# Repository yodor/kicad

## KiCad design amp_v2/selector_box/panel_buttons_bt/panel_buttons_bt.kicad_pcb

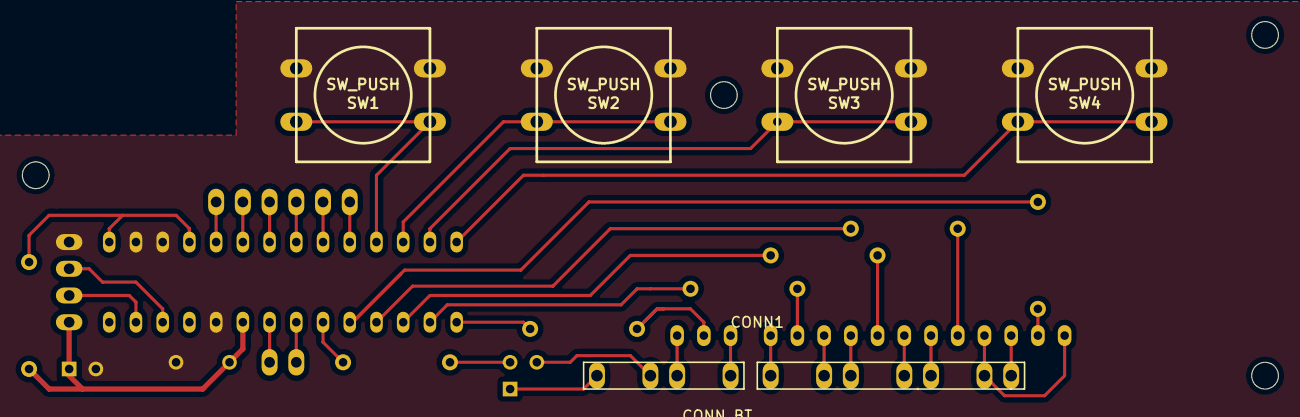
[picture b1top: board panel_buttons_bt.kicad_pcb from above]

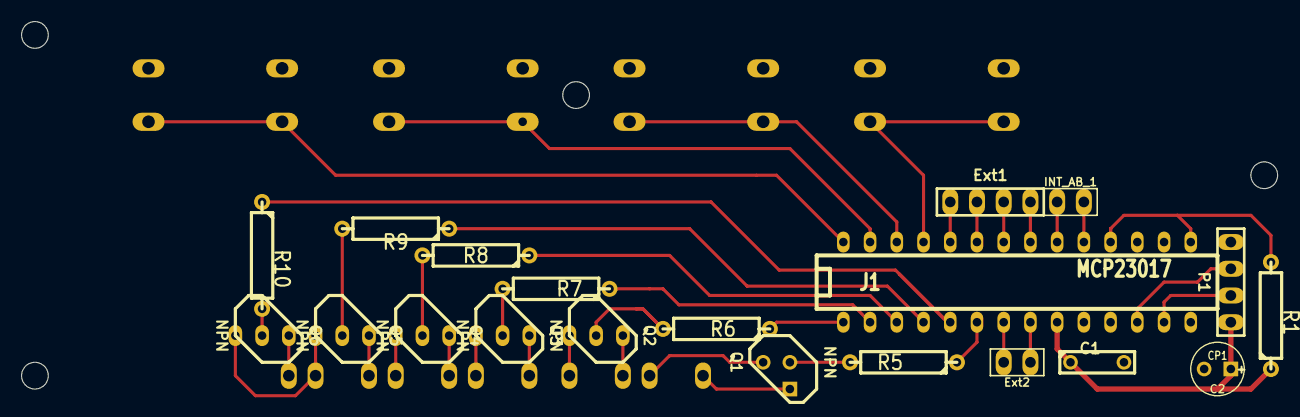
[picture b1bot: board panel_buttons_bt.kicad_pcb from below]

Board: 2 copper layers, 119.4 x 34.9 mm, 25 parts (20 on the bottom side), 40 nets.

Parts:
C1: 100nF; C2
C2: CP1; C1V5
CONN1: CONN_BT
Ext1: CONN_4; PIN_ARRAY_4x1
Ext2: CONN_2; PIN_ARRAY_2X1
INT_AB_1: CONN_2; PIN_ARRAY_2X1
J1: MCP23017; DIP-28__300
P1: CONN_4; PIN_ARRAY_4x1
Q1, Q2, Q3, Q4, Q5, Q6: NPN; TO92-123
R1, R5, R6, R7, R8, R9, R10: 10K; R4
SW1, SW2, SW3, SW4: SW_PUSH; SW_PUSH-12mm

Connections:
/5V: C1.1, C2.1, J1.9, P1.1, R1.1
/BTN1: J1.25, SW1.1
/BTN2: J1.26, SW2.1
/BTN3: J1.27, SW3.1
/BTN4: J1.28, SW4.1
/BT_BACK: J1.2, R7.1
/BT_FWD: J1.1, R6.1
/BT_PLPP: J1.5, R10.1
/BT_PWR: J1.6, R5.1
/BT_VOLDN: J1.4, R9.1
/BT_VOLUP: J1.3, R8.1
/SCL: J1.12, P1.3
/SDA: J1.13, P1.2
DGND: C1.2, C2.2, J1.10, J1.16, J1.17, P1.4, SW1.2, SW2.2, SW3.2, SW4.2
unnamed: Q3.2, R7.2
unnamed: CONN1.back, Q3.1
unnamed: CONN1.v_up, Q4.1
unnamed: CONN1.v_dn, Q5.1
unnamed: CONN1.play, Q6.1
unnamed: CONN1.1V81, Q2.3
unnamed: Q2.2, R6.2
unnamed: CONN1.fwd, Q2.1
unnamed: CONN1.1V82, Q3.3
unnamed: CONN1.pwr2, Q1.1
unnamed: Q4.2, R8.2
unnamed: Q5.2, R9.2
unnamed: Q6.2, R10.2
unnamed: CONN1.1V84, Q5.3, Q6.3
unnamed: CONN1.1V83, Q4.3
unnamed: Ext1.3, J1.22
unnamed: Ext1.1, J1.24
unnamed: Ext1.2, J1.23
unnamed: Ext1.4, J1.21
unnamed: INT_AB_1.1, J1.20
unnamed: INT_AB_1.2, J1.19
unnamed: Ext2.2, J1.7
unnamed: Ext2.1, J1.8
unnamed: J1.15, J1.18, R1.2
unnamed: Q1.2, R5.2
unnamed: CONN1.pwr1, Q1.3

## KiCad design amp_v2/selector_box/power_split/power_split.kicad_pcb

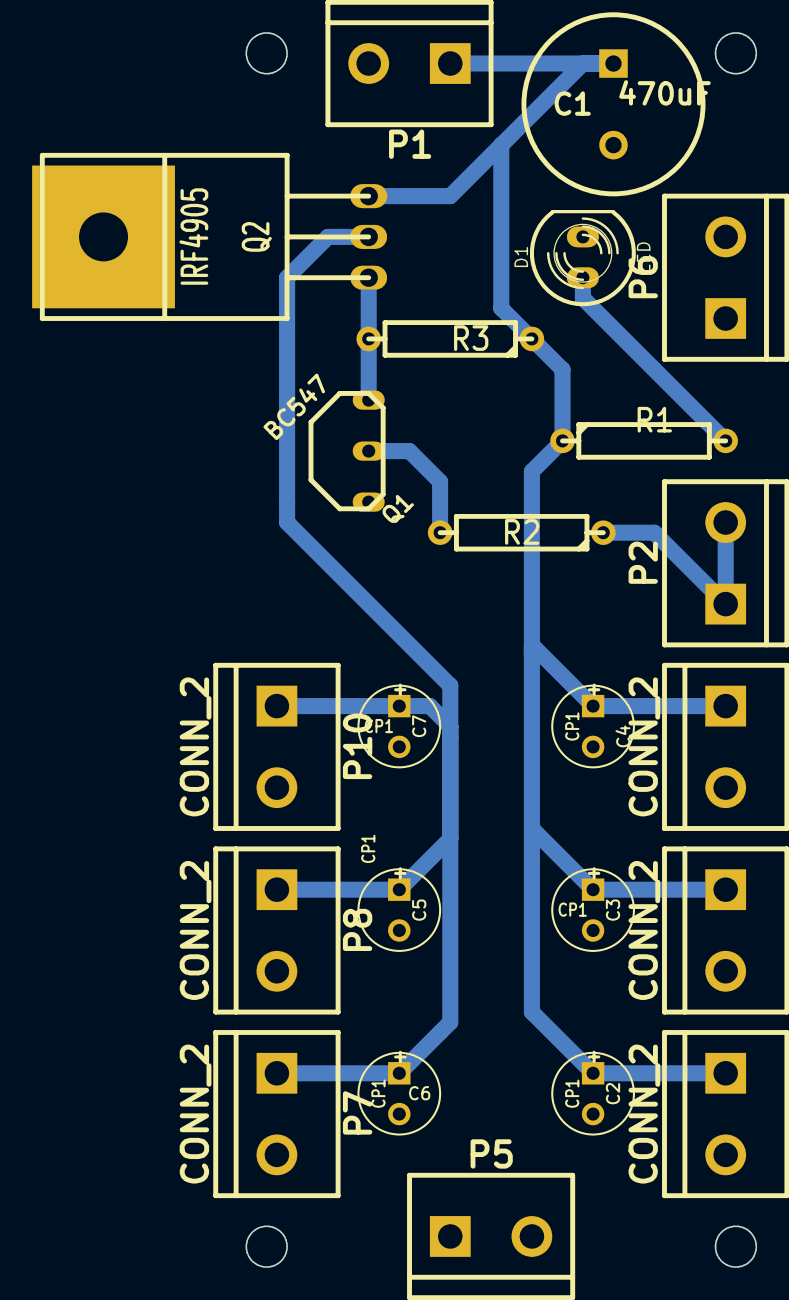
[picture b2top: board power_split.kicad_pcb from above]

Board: 2 copper layers, 31.8 x 76.8 mm, 23 parts (0 on the bottom side), 7 nets.

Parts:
C1: 470uF; C2V10
C2, C3, C4, C5, C6, C7: CP1; C1V5
D1: LED; LED-5MM
P1, P2, P3, P4, P5, P6, P7, P8, P9, P10: CONN_2; bornier2
Q1: BC547; TO92
Q2: IRF4905; TO220GDS
R1: 680R / 0.5W; R4
R2, R3: 10K; R4

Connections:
/12V: C1.1, C2.1, C3.1, C4.1, P1.1, P3.1, P4.1, P9.1, Q2.S, R1.1, R3.1
/12V_EN: P2.1, P2.2, R2.1
/12V_SW: C5.1, C6.1, C7.1, P7.1, P8.1, P10.1, Q2.D
GND: C1.2, C2.2, C3.2, C4.2, C5.2, C6.2, C7.2, D1.2, P1.2, P3.2, P4.2, P5.1, P5.2, P6.1, P6.2, P7.2, P8.2, P9.2, P10.2, Q1.3
unnamed: Q1.2, R2.2
unnamed: D1.1, R1.2
unnamed: Q1.1, Q2.G, R3.2

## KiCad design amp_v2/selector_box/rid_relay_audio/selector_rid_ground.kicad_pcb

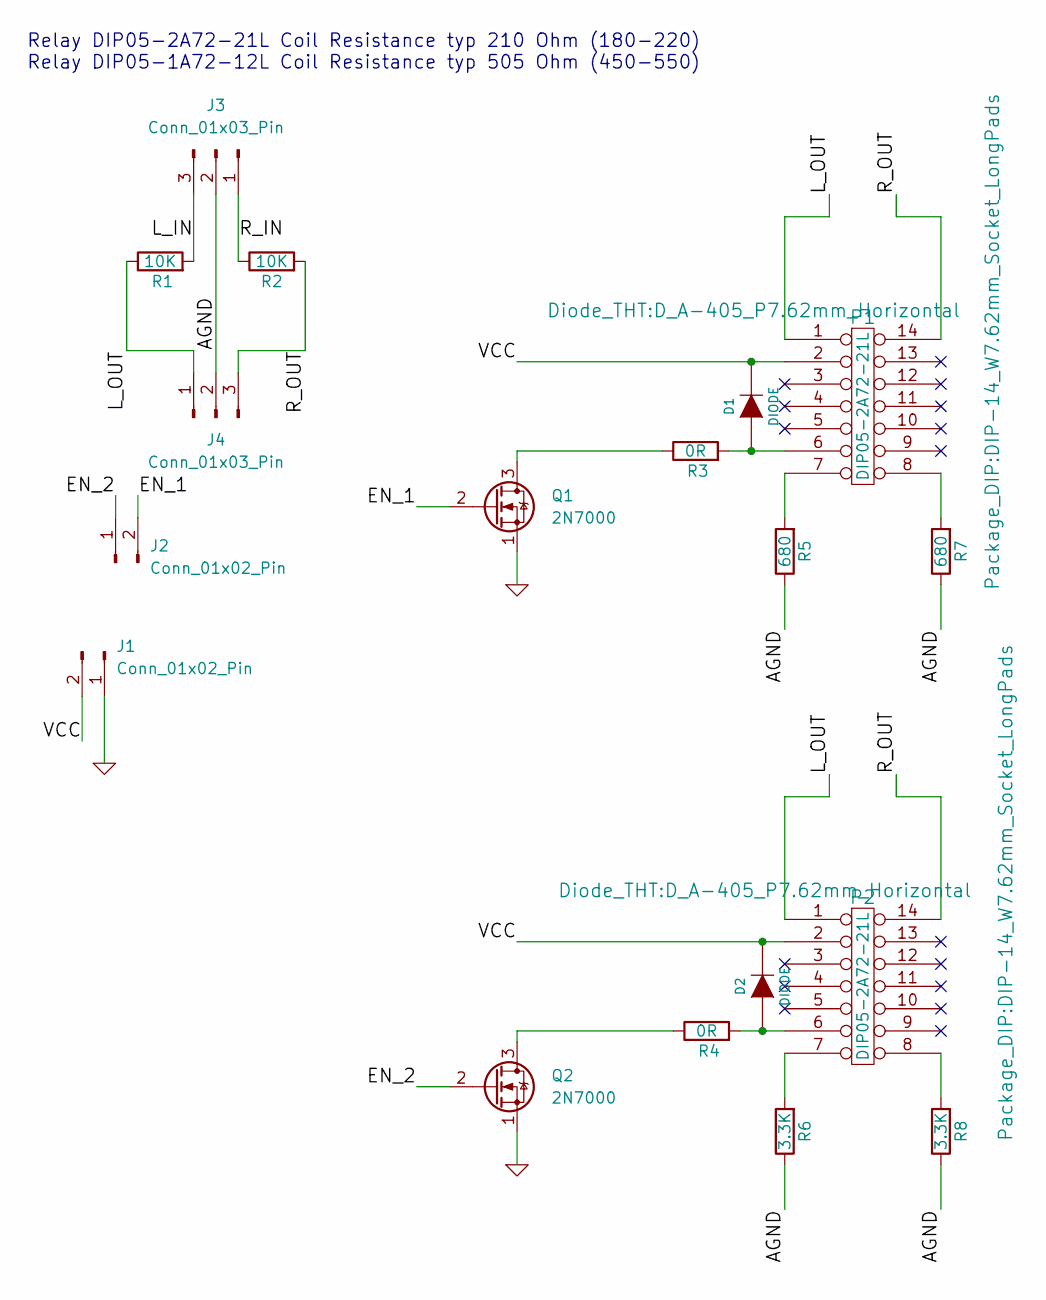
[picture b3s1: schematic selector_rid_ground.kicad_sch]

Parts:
D1, D2: DIODE; D_A-405_P7.62mm_Horizontal
J1, J2: Conn_01x02_Pin; PinHeader_1x02_P2.54mm_Vertical
J3, J4: Conn_01x03_Pin; JST_XH_B3B-XH-A_1x03_P2.50mm_Vertical
P1, P2: DIP05-2A72-21L; DIP-14_W7.62mm_Socket_LongPads
Q1, Q2: 2N7000; TO-92L_Inline_Wide
R1, R2: 10K; R_Axial_DIN0207_L6.3mm_D2.5mm_P7.62mm_Horizontal
R3, R4: 0R; R_Axial_DIN0207_L6.3mm_D2.5mm_P7.62mm_Horizontal
R5: 680; R_Axial_DIN0207_L6.3mm_D2.5mm_P7.62mm_Horizontal
R6: 3.3K; R_Axial_DIN0207_L6.3mm_D2.5mm_P7.62mm_Horizontal
R7: 680; R_Axial_DIN0204_L3.6mm_D1.6mm_P2.54mm_Vertical
R8: 3.3K; R_Axial_DIN0204_L3.6mm_D1.6mm_P2.54mm_Vertical

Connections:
/AGND: J3.2, J4.2, R5.1, R6.1, R7.1, R8.1
/EN_1: J2.2, Q1.2 (G)
/EN_2: J2.1, Q2.2 (G)
/L_IN: J3.3, R1.2
/L_OUT: J4.1, P1.1, P2.1, R1.1
/R_IN: J3.1, R2.1
/R_OUT: J4.3, P1.14, P2.14, R2.2
/VCC: D1.2 (K), D2.2 (K), J1.2, P1.2, P2.2
GND: J1.1, Q1.1 (S), Q2.1 (S)
unnamed: D1.1 (A), P1.6, R3.2
unnamed: D2.1 (A), P2.6, R4.2
unnamed: P1.7, R5.2
unnamed: P1.8, R7.2
unnamed: P2.7, R6.2
unnamed: P2.8, R8.2
unnamed: Q1.3 (D), R3.1
unnamed: Q2.3 (D), R4.1

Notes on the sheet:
Relay DIP05-2A72-21L Coil Resistance typ 210 Ohm (180-220) Relay DIP05-1A72-12L Coil Resistance typ 505 Ohm (450-550)

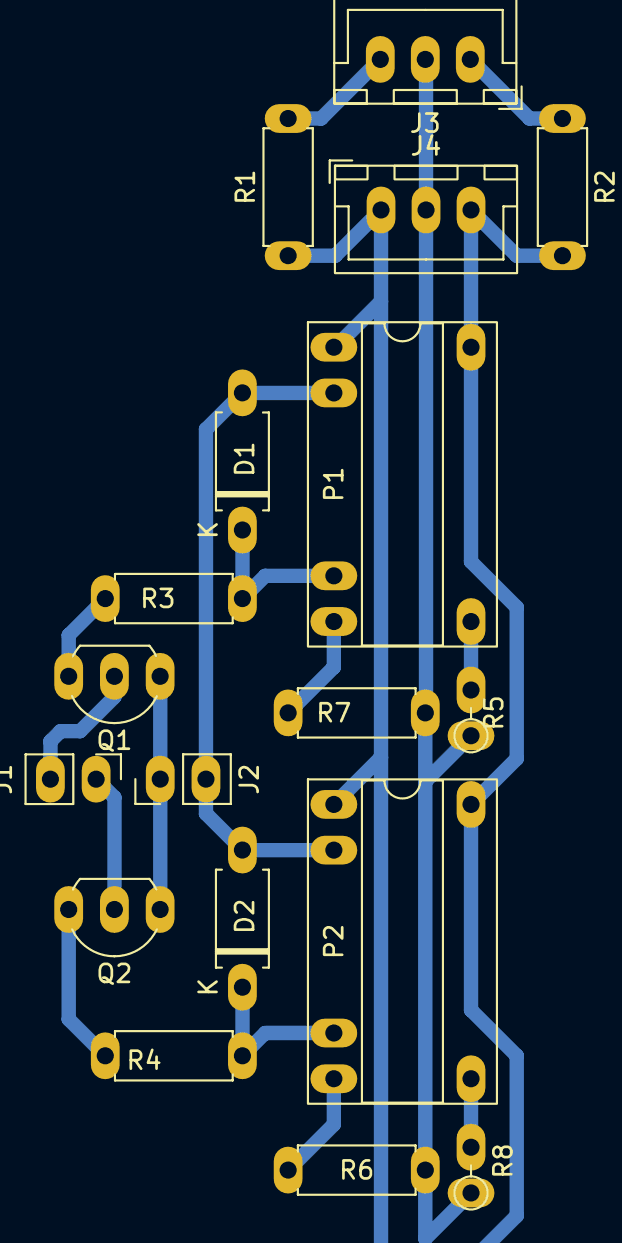
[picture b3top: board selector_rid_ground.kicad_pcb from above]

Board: 2 copper layers, 18 parts (0 on the bottom side), 17 nets.

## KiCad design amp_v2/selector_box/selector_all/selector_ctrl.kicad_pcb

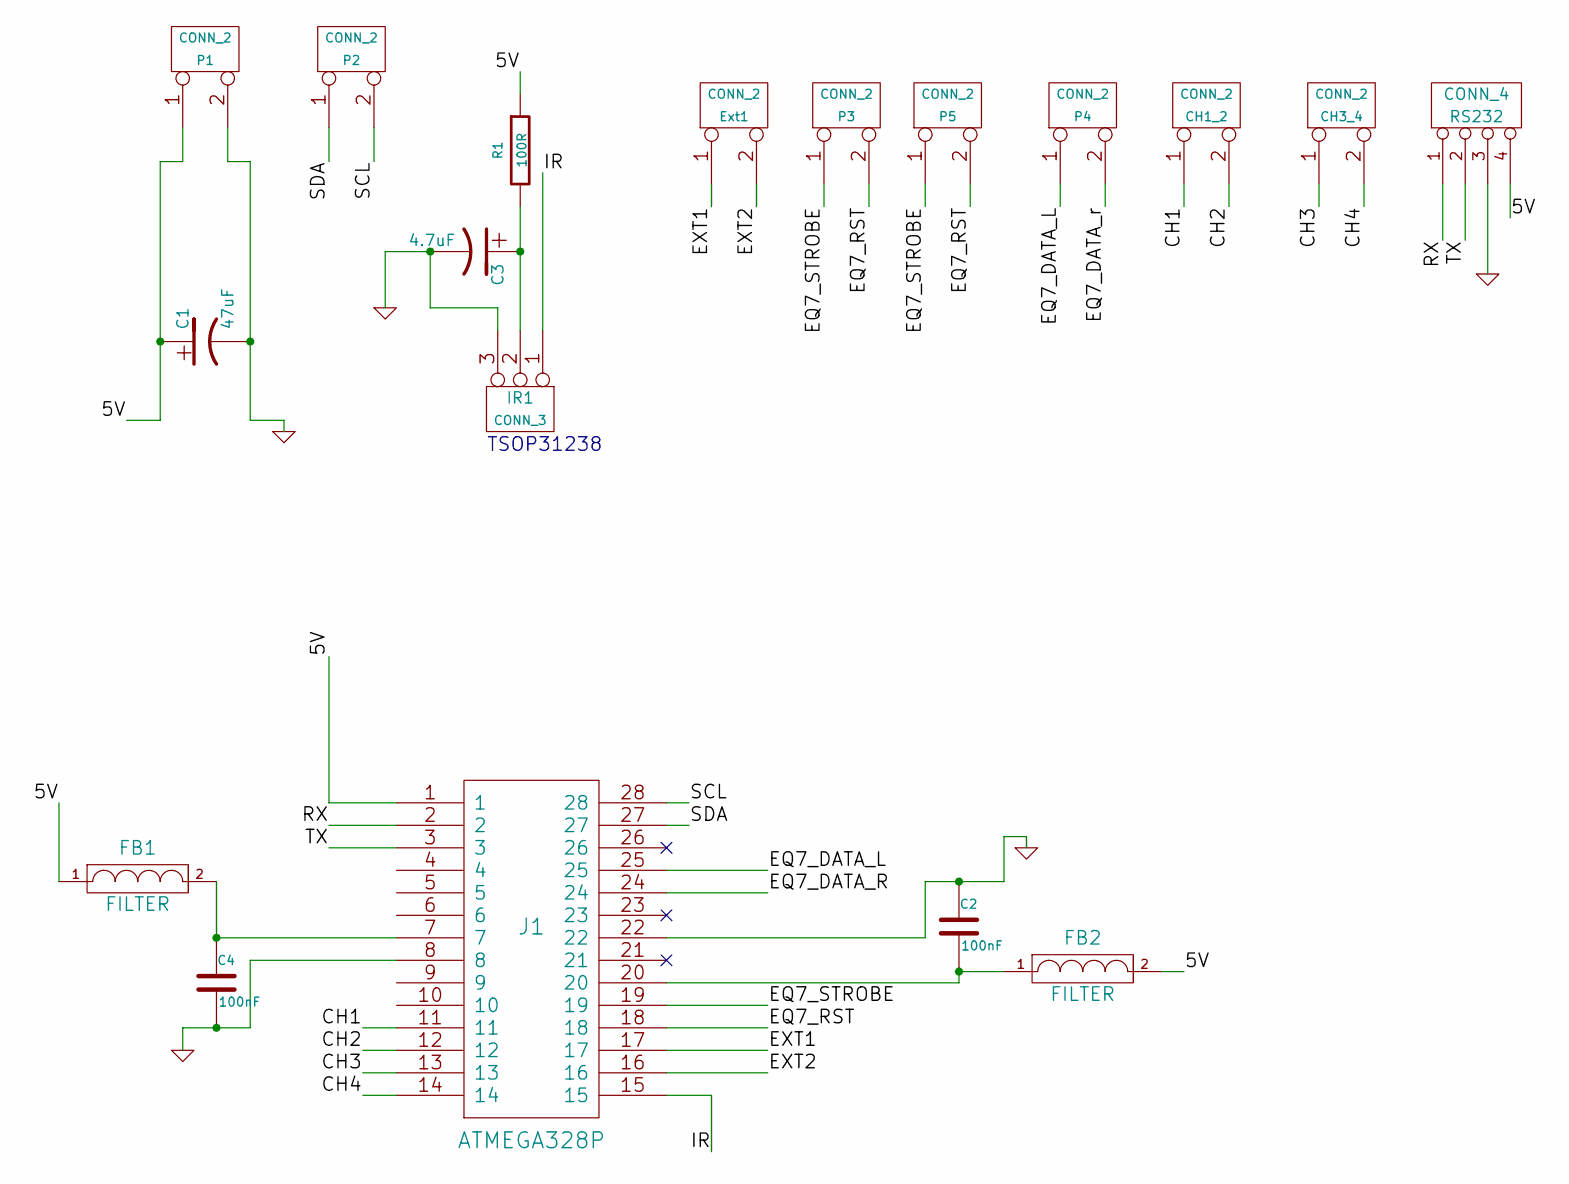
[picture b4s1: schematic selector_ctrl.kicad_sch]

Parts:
C1: 47uF
C2, C4: 100nF
C3: 4.7uF
CH1_2, CH3_4: CONN_2
Ext1: CONN_2
FB1, FB2: FILTER
IR1: CONN_3
J1: ATMEGA328P
P1, P2, P3, P4, P5: CONN_2
R1: 100R
RS232: CONN_4

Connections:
/5V: C1.1, FB1.1, FB2.2, J1.1, P1.1, R1.1, RS232.4
/CH1: CH1_2.1, J1.11
/CH2: CH1_2.2 (PM), J1.12
/CH3: CH3_4.1, J1.13
/CH4: CH3_4.2 (PM), J1.14
/EQ7_DATA_L: J1.25, P4.1
/EQ7_DATA_R: J1.24, P4.2 (PM)
/EQ7_RST: J1.18, P3.2 (PM), P5.2 (PM)
/EQ7_STROBE: J1.19, P3.1, P5.1
/EXT1: Ext1.1, J1.17
/EXT2: Ext1.2 (PM), J1.16
/IR: IR1.1, J1.15
/RX: J1.2, RS232.1
/SCL: J1.28, P2.2 (PM)
/SDA: J1.27, P2.1
/TX: J1.3, RS232.2
GND: C1.2, C2.1, C3.2, C4.2, IR1.3, J1.8, J1.22, P1.2 (PM), RS232.3
unnamed: C2.2, FB2.1, J1.20
unnamed: C4.1, FB1.2, J1.7
unnamed: C3.1, IR1.2 (PM), R1.2

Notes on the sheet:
TSOP31238

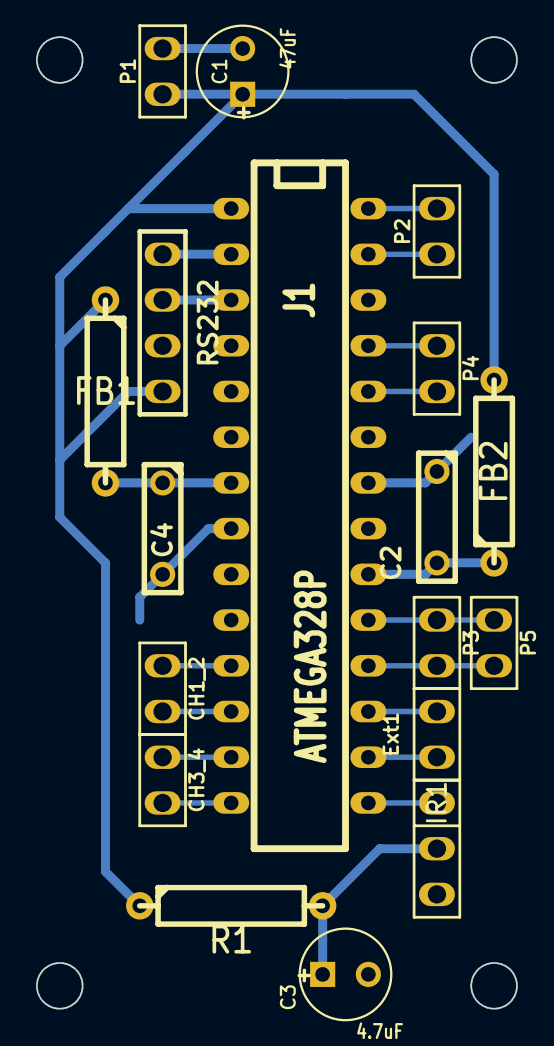
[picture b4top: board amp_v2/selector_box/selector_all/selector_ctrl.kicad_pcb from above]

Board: 2 copper layers, 26.7 x 54.0 mm, 18 parts (0 on the bottom side), 20 nets.

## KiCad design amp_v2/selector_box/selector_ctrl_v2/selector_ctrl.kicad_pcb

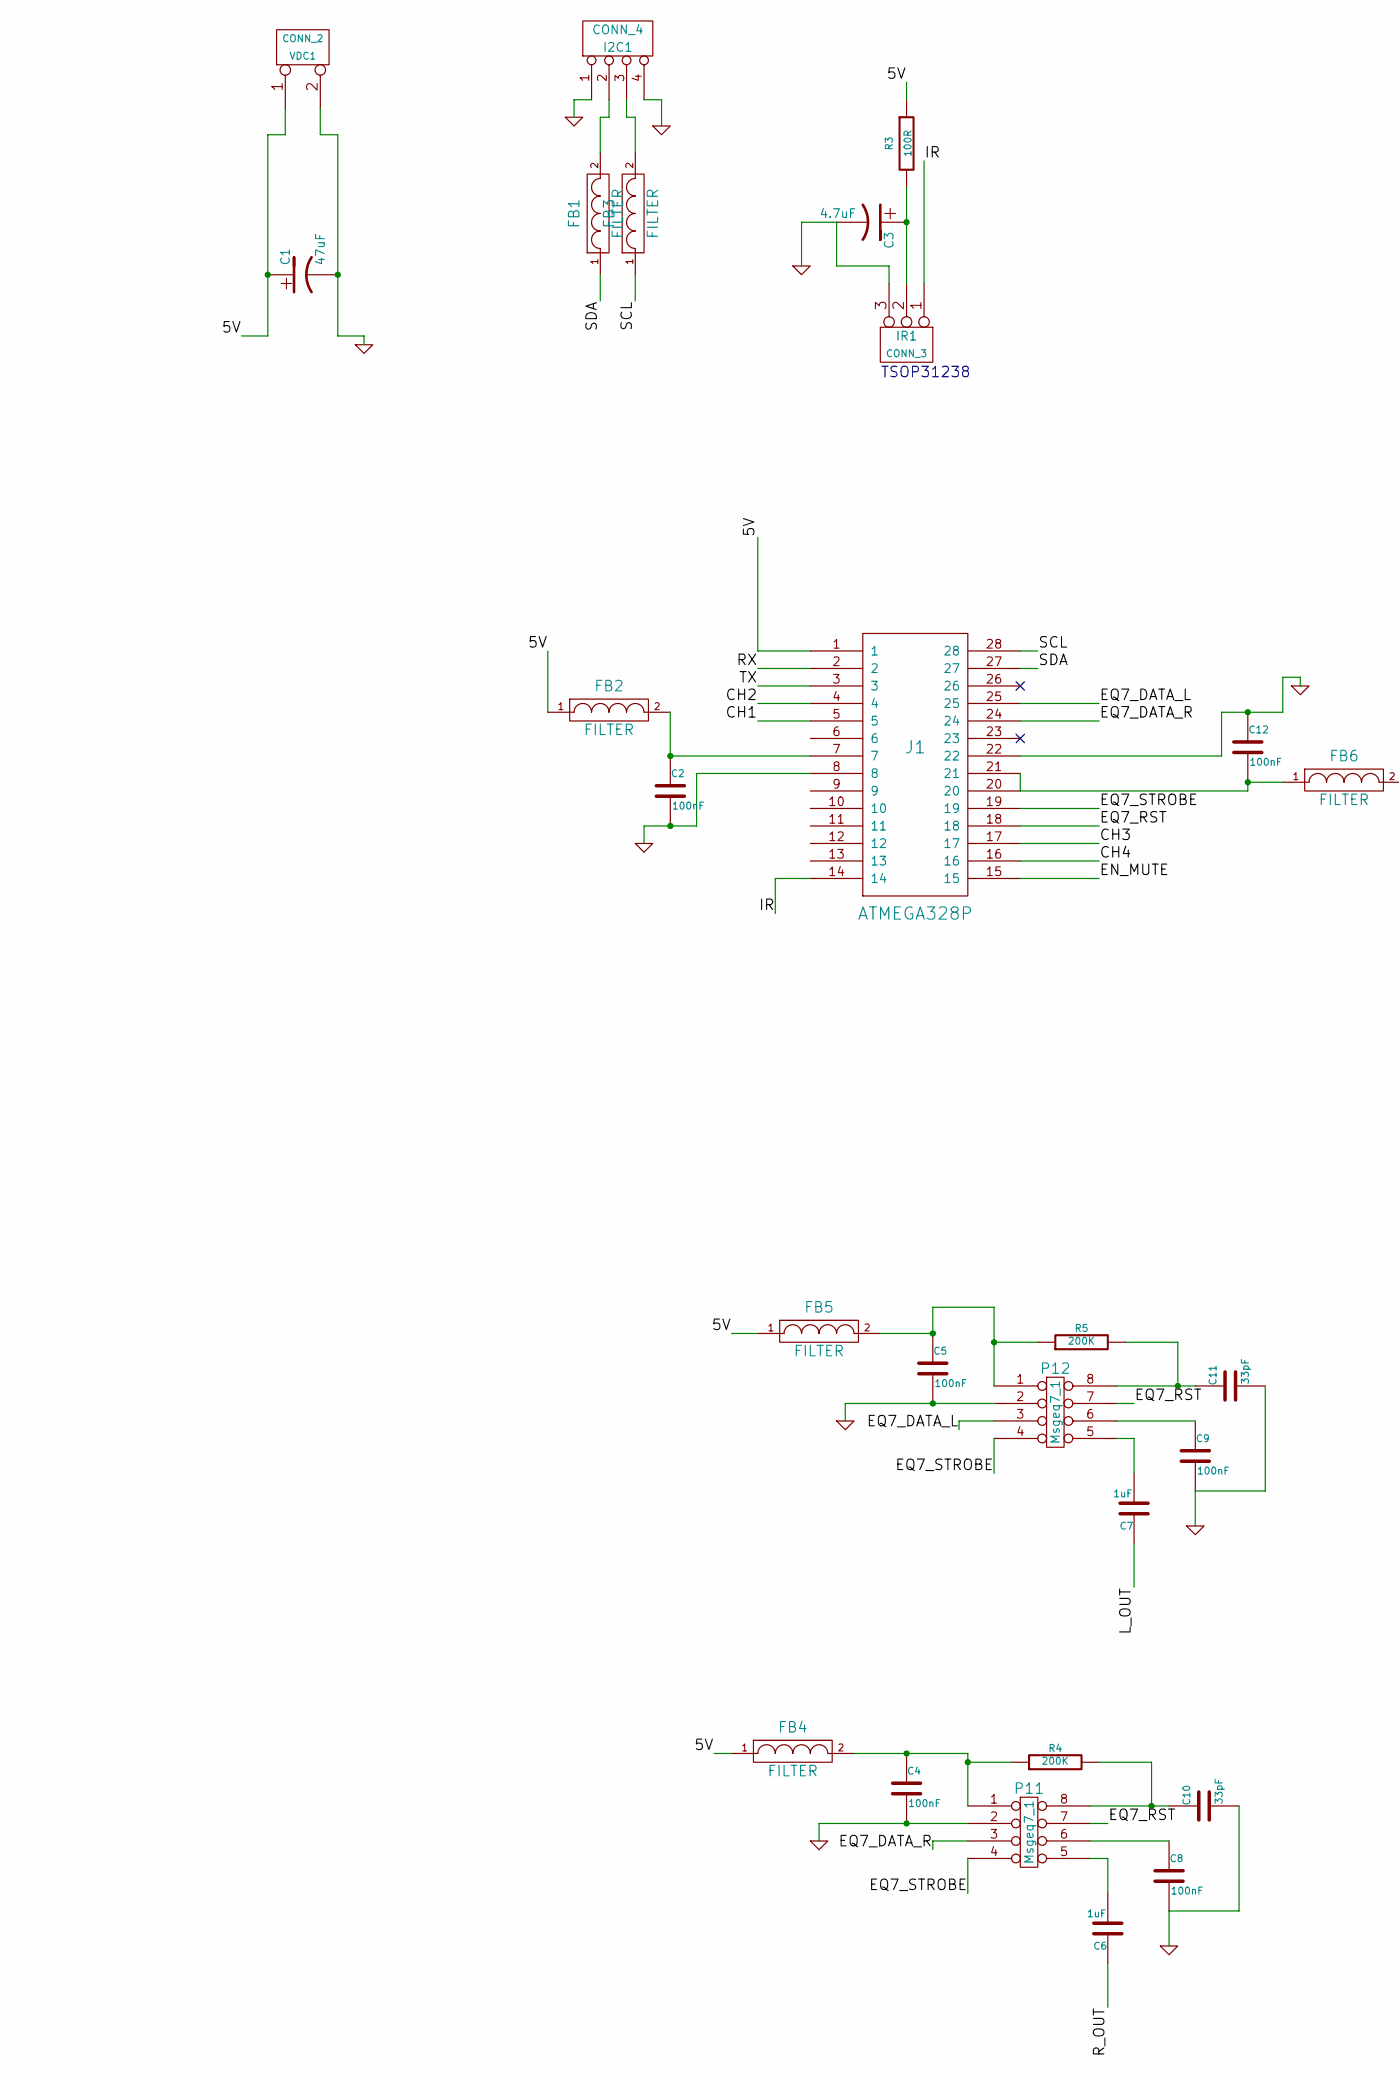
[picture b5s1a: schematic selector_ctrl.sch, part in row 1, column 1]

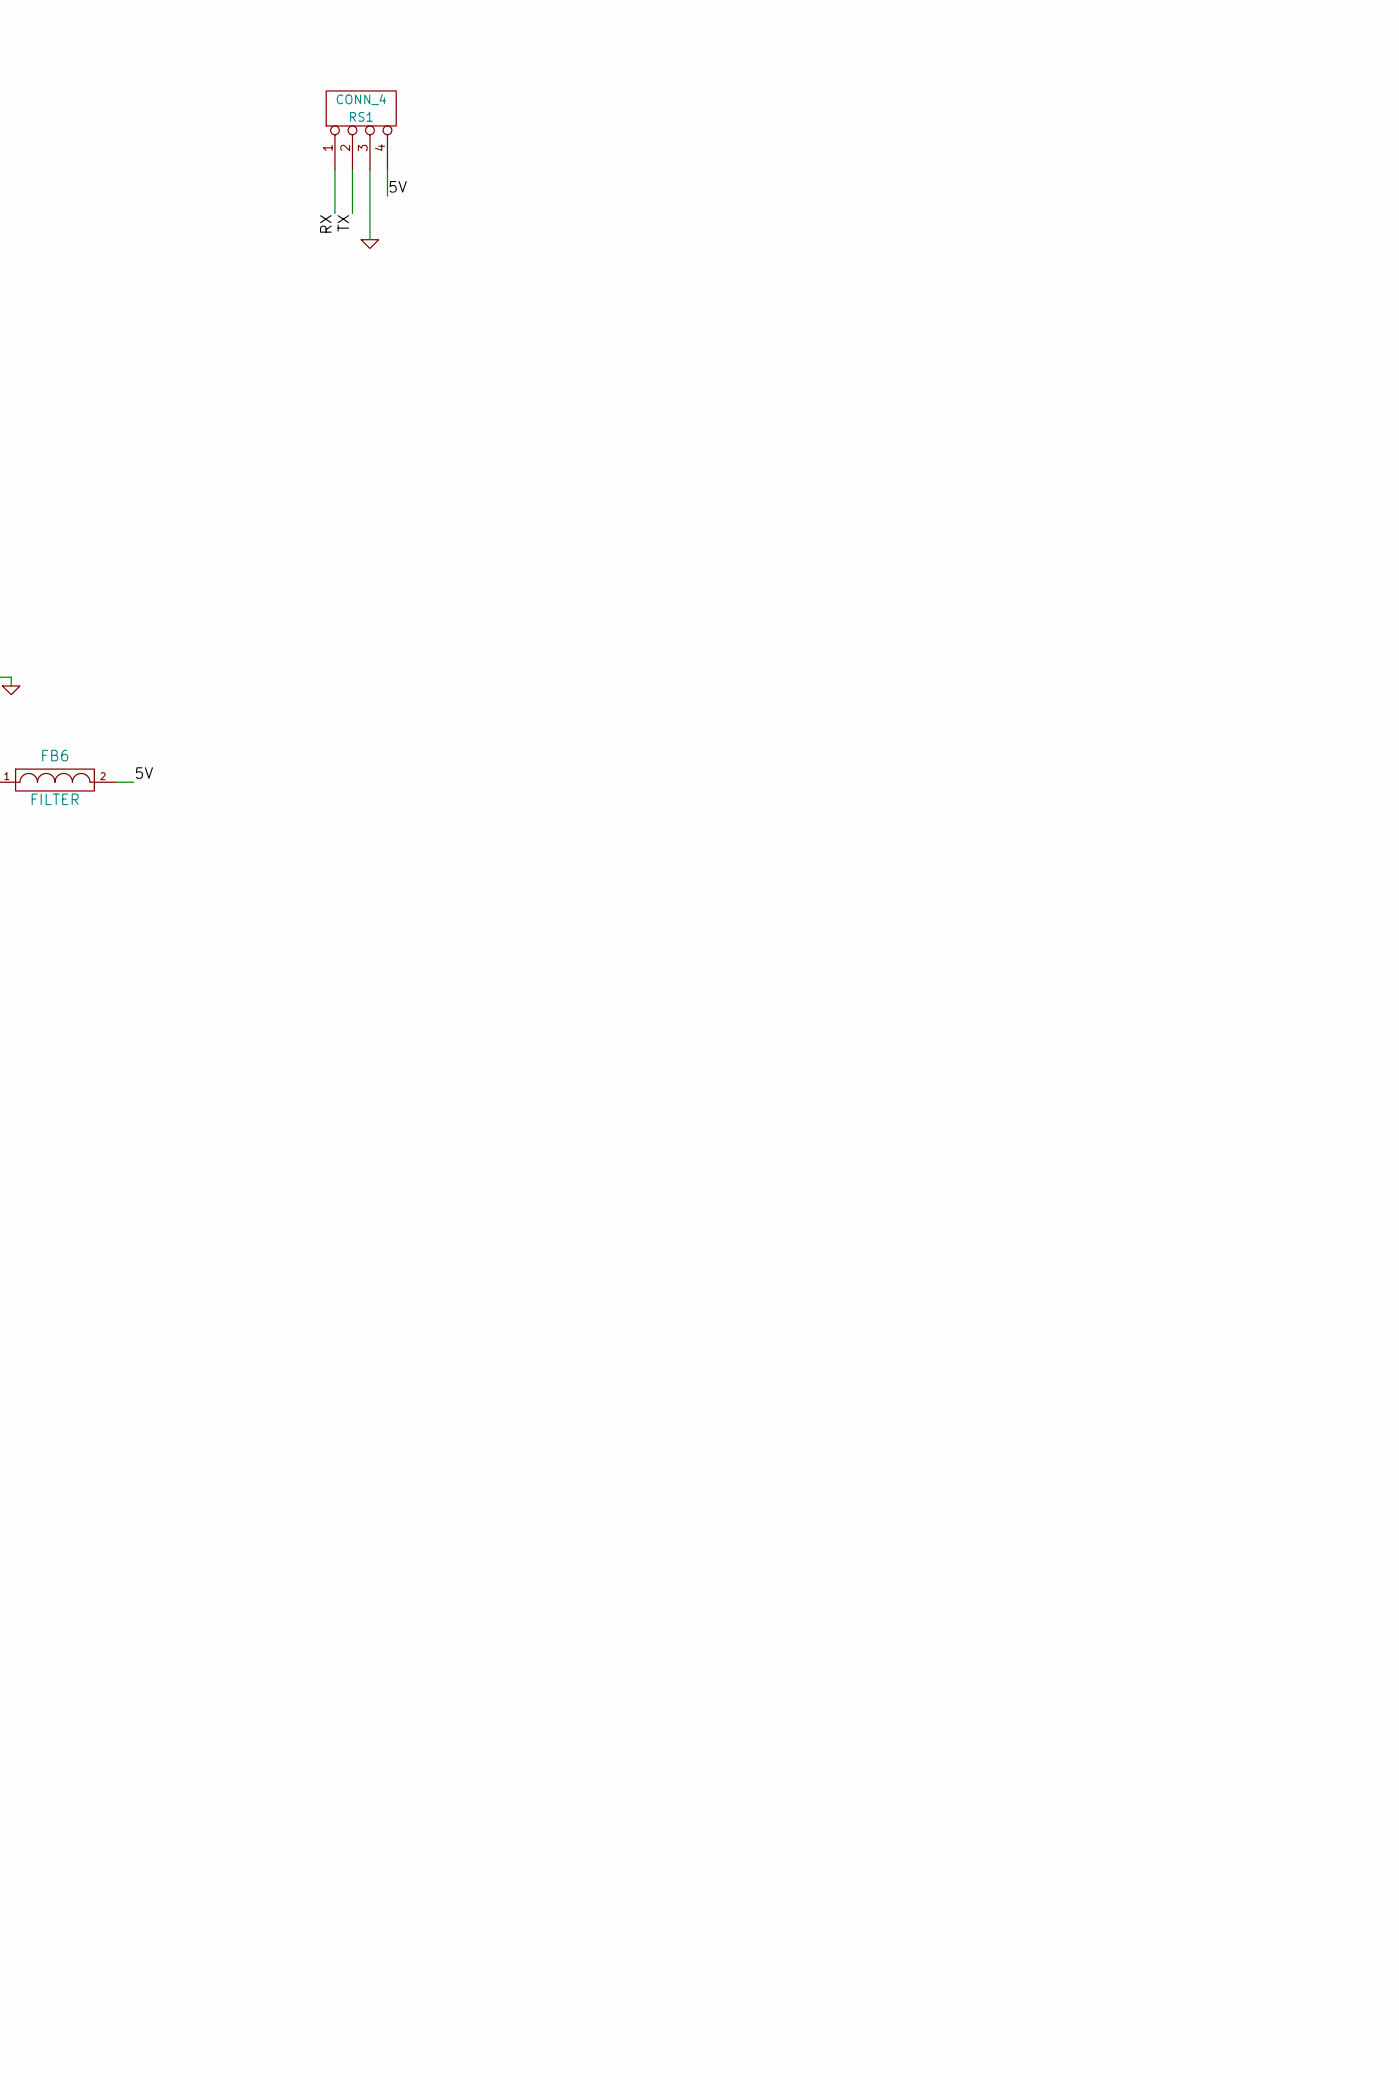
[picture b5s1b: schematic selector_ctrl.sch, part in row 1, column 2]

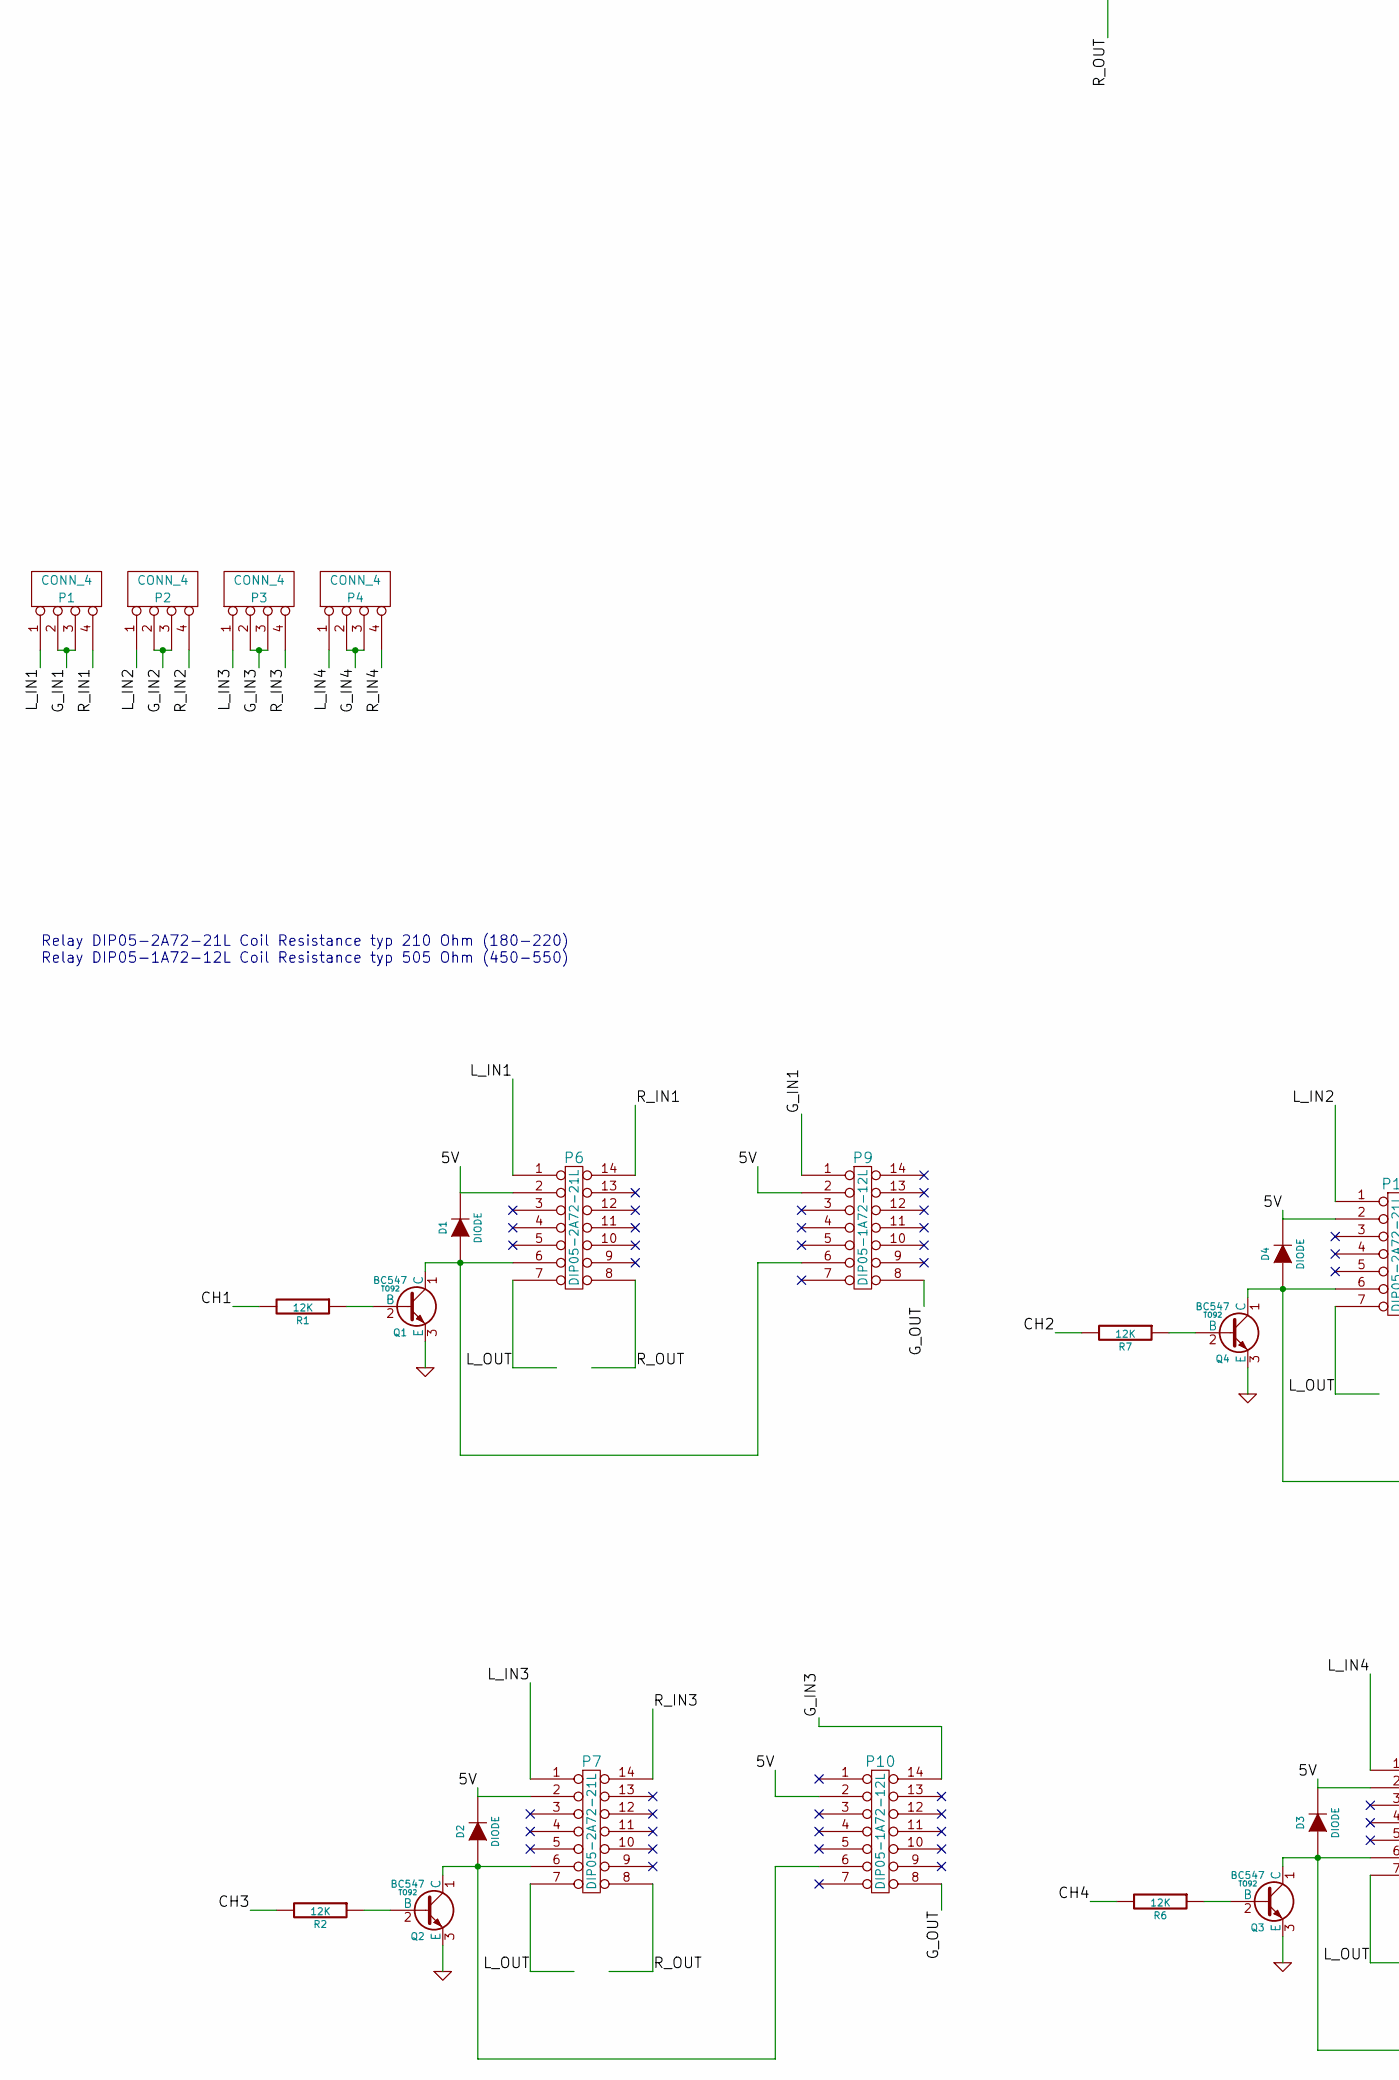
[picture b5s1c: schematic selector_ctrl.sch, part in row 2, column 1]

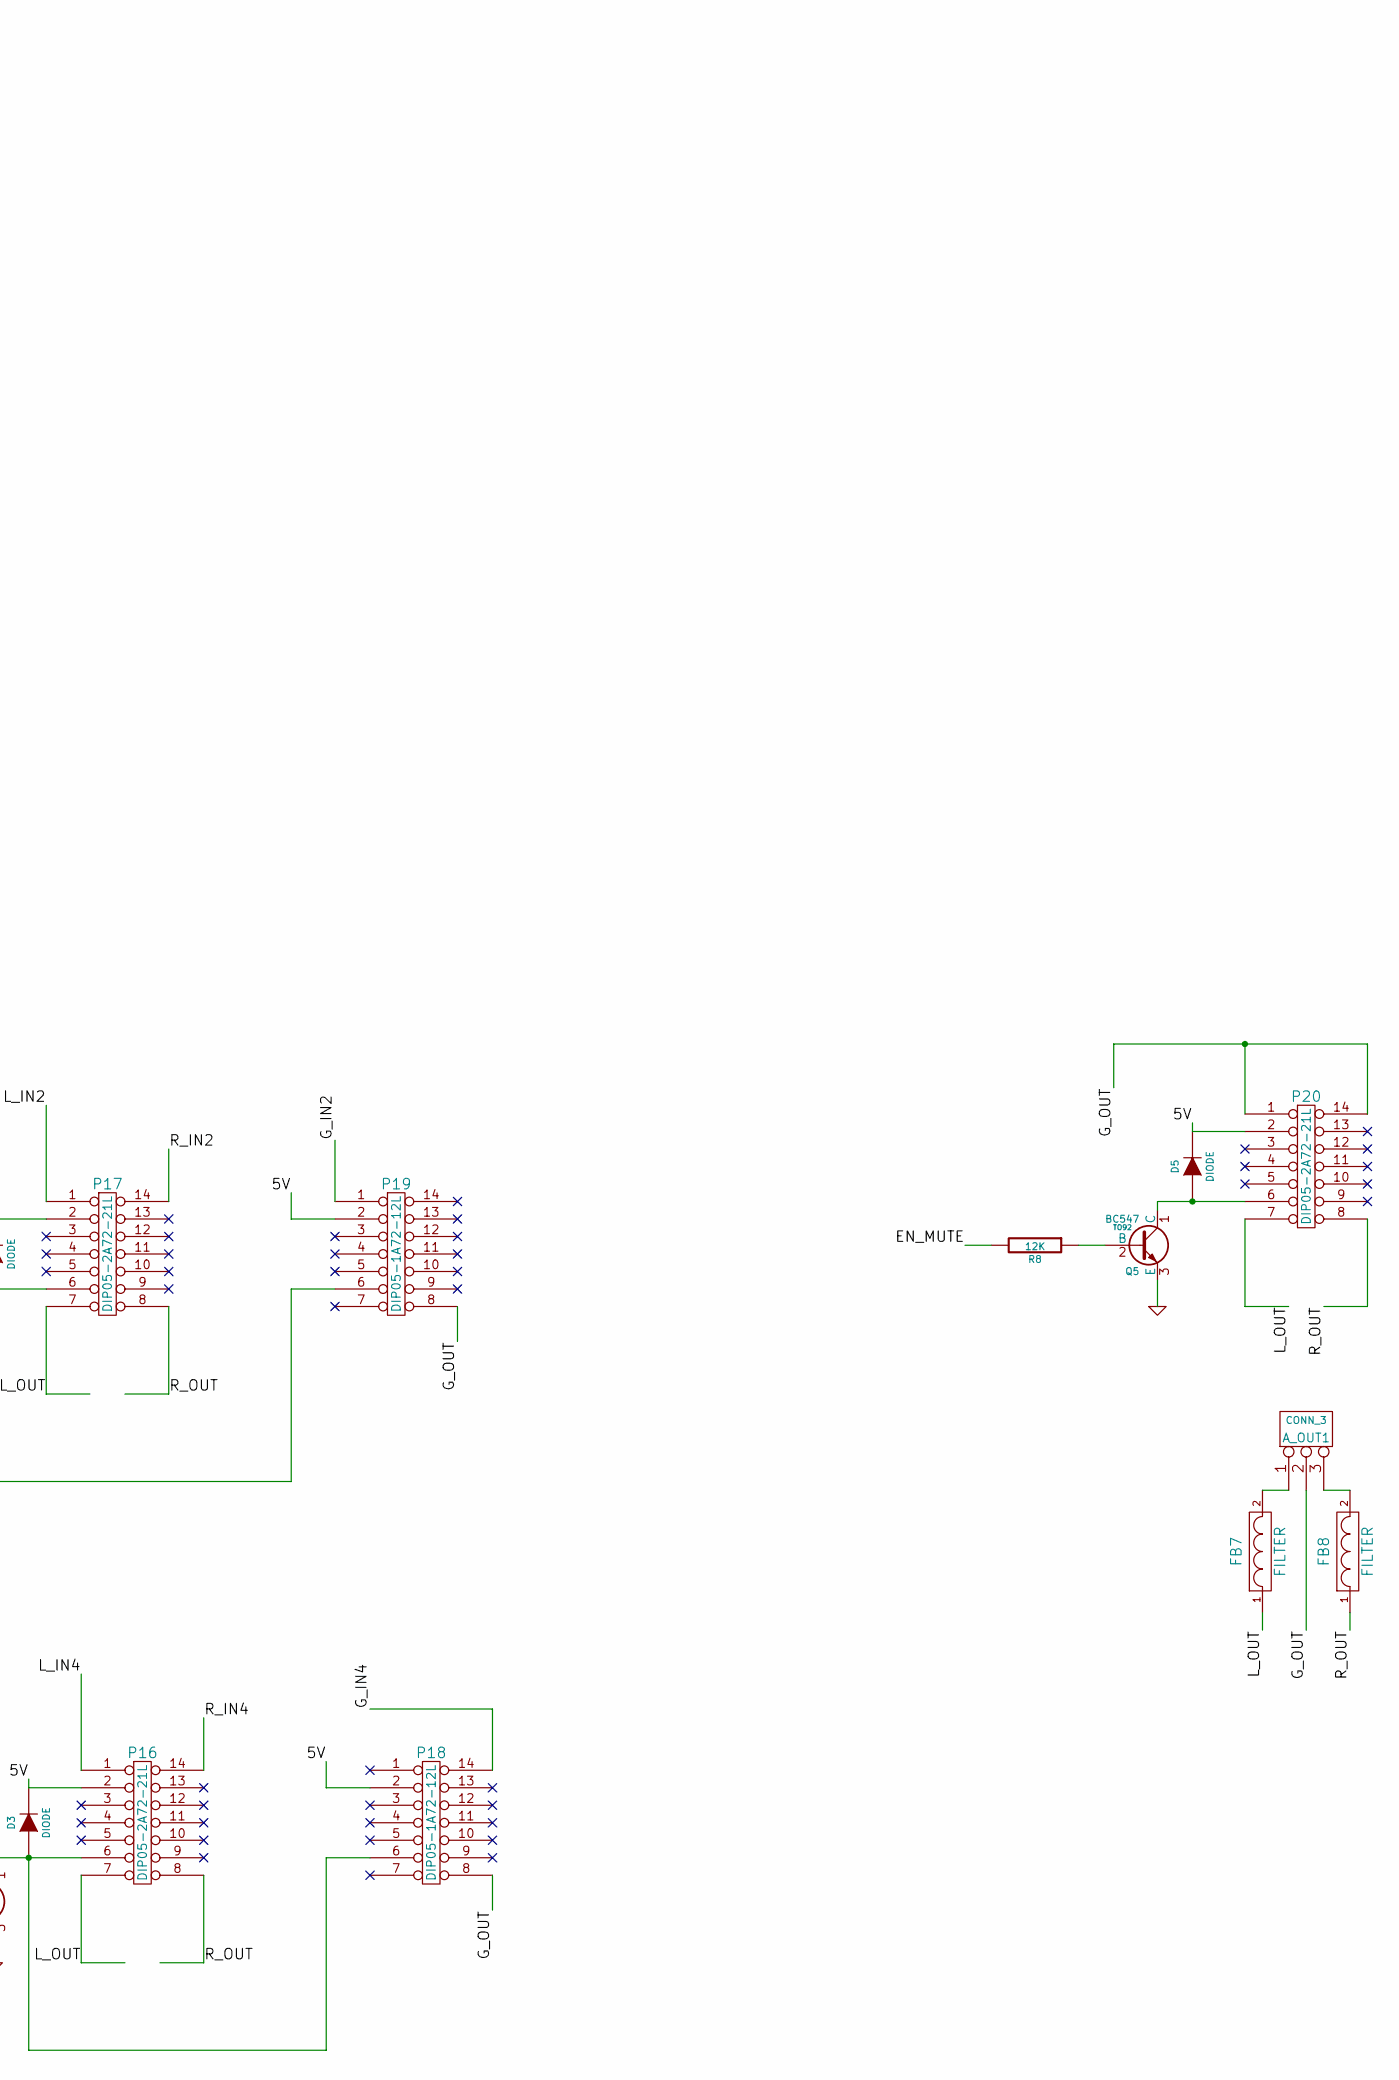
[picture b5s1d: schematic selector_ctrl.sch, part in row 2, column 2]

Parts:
A_OUT1: CONN_3
C1: 47uF
C2, C4, C5, C8, C9, C12: 100nF
C3: 4.7uF
C6, C7: 1uF
C10, C11: 33pF
D1, D2, D3, D4, D5: DIODE
FB1, FB2, FB3, FB4, FB5, FB6, FB7, FB8: FILTER
I2C1: CONN_4
IR1: CONN_3
J1: ATMEGA328P
P1, P2, P3, P4: CONN_4
P6, P7, P16, P17, P20: DIP05-2A72-21L
P9, P10, P18, P19: DIP05-1A72-12L
P11, P12: Msgeq7_1
Q1, Q2, Q3, Q4, Q5: BC547; TO92
R1, R2, R6, R7, R8: 12K
R3: 100R
R4, R5: 200K
RS1: CONN_4
VDC1: CONN_2

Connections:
/5V: C1.1, D1.2 (K), D2.2 (K), D3.2 (K), D4.2 (K), D5.2 (K), FB2.1, FB4.1, FB5.1, FB6.2, J1.1, P6.2, P7.2, P9.2, P10.2, P16.2, P17.2, P18.2, P19.2, P20.2, R3.1, RS1.4, VDC1.1
/CH1: J1.5, R1.2
/CH2: J1.4, R7.2
/CH3: J1.17, R2.2
/CH4: J1.16, R6.2
/EN_MUTE: J1.15, R8.2
/EQ7_DATA_L: J1.25, P12.3
/EQ7_DATA_R: J1.24, P11.3
/EQ7_RST: J1.18, P11.7, P12.7
/EQ7_STROBE: J1.19, P11.4, P12.4
/G_IN1: P1.2, P1.3, P9.1
/G_IN2: P2.2, P2.3, P19.1
/G_IN3: P3.2, P3.3, P10.14
/G_IN4: P4.2, P4.3, P18.14
/G_OUT: A_OUT1.2 (PM), P9.8, P10.8, P18.8, P19.8, P20.1, P20.14
/IR: IR1.1, J1.14
/L_IN1: P1.1, P6.1
/L_IN2: P2.1, P17.1
/L_IN3: P3.1, P7.1
/L_IN4: P4.1, P16.1
/L_OUT: C7.1, FB7.1, P6.7, P7.7, P16.7, P17.7, P20.7
/RX: J1.2, RS1.1
/R_IN1: P1.4, P6.14
/R_IN2: P2.4, P17.14
/R_IN3: P3.4, P7.14
/R_IN4: P4.4, P16.14
/R_OUT: C6.1, FB8.1, P6.8, P7.8, P16.8, P17.8, P20.8
/SCL: FB3.1, J1.28
/SDA: FB1.1, J1.27
/TX: J1.3, RS1.2
GND: C1.2, C2.2, C3.2, C4.2, C5.2, C8.2, C9.2, C10.2, C11.2, C12.1, I2C1.1, I2C1.4, IR1.3, J1.8, J1.22, P11.2, P12.2, Q1.3 (E), Q2.3 (E), Q3.3 (E), Q4.3 (E), Q5.3 (E), RS1.3, VDC1.2 (PM)
unnamed: Q4.2 (B), R7.1
unnamed: Q2.2 (B), R2.1
unnamed: D2.1 (A), P7.6, P10.6, Q2.1 (C)
unnamed: D3.1 (A), P16.6, P18.6, Q3.1 (C)
unnamed: C12.2, FB6.1, J1.20, J1.21
unnamed: Q5.2 (B), R8.1
unnamed: D5.1 (A), P20.6, Q5.1 (C)
unnamed: D4.1 (A), P17.6, P19.6, Q4.1 (C)
unnamed: A_OUT1.3, FB8.2
unnamed: A_OUT1.1, FB7.2
unnamed: C2.1, FB2.2, J1.7
unnamed: C7.2, P12.5
unnamed: C9.1, P12.6
unnamed: C11.1, P12.8, R5.2
unnamed: FB1.2, I2C1.2
unnamed: FB3.2, I2C1.3
unnamed: C5.1, FB5.2, P12.1, R5.1
unnamed: C3.1, IR1.2 (PM), R3.2
unnamed: Q1.2 (B), R1.1
unnamed: Q3.2 (B), R6.1
unnamed: D1.1 (A), P6.6, P9.6, Q1.1 (C)
unnamed: C6.2, P11.5
unnamed: C8.1, P11.6
unnamed: C10.1, P11.8, R4.2
unnamed: C4.1, FB4.2, P11.1, R4.1

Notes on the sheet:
TSOP31238
Relay DIP05-2A72-21L Coil Resistance typ 210 Ohm (180-220) Relay DIP05-1A72-12L Coil Resistance typ 505 Ohm (450-550)
